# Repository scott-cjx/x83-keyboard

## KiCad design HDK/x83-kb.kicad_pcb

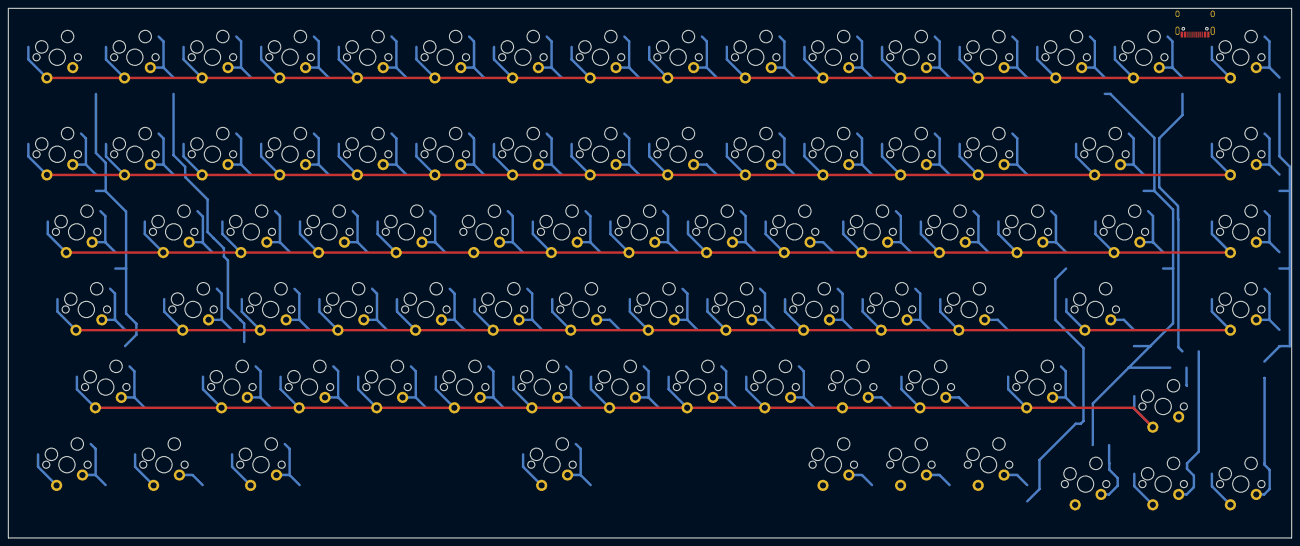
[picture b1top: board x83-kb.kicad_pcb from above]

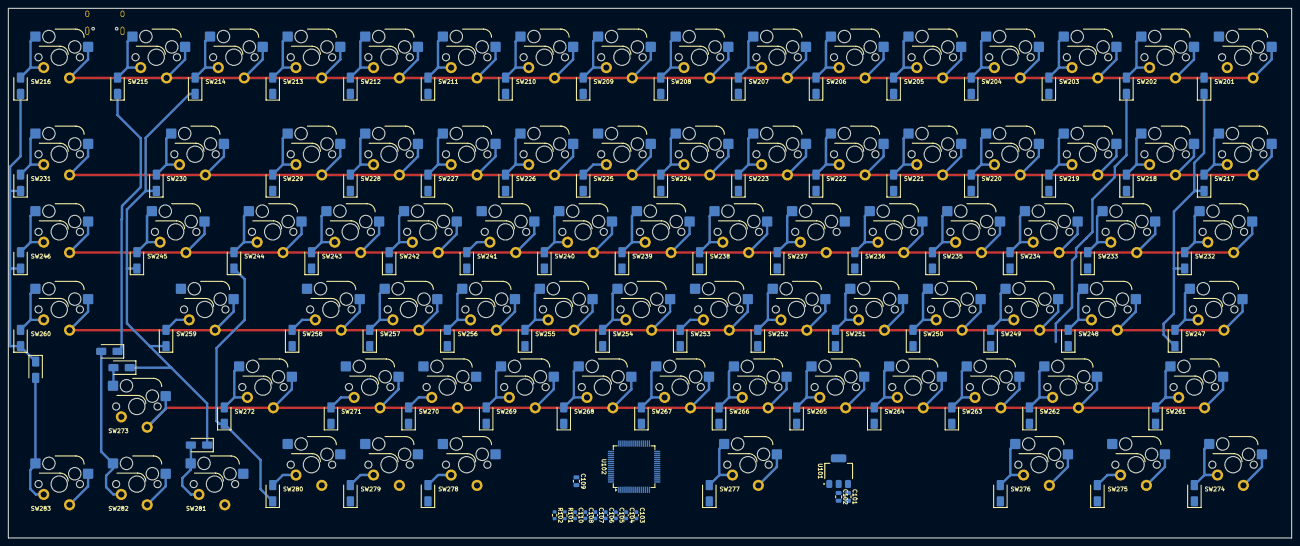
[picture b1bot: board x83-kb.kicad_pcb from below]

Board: 2 copper layers, 315.0 x 130.0 mm, 180 parts (97 on the bottom side), 110 nets.

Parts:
C101, C102, C109: 2u2; C_0805_2012Metric
C103, C104, C105, C106, C107, C108, C110: 100n; C_0603_1608Metric
D201, D202, D203, D204, D205, D206, D207, D208, D209, D210, D211, D212, D213, D214, D215, D216, D217, D218, D219, D220, D221, D222, D223, D224, D225, D226, D227, D228, D229, D230, D231, D232, D233, D234, D235, D236, D237, D238, D239, D240, D241, D242, D243, D244, D245, D246, D247, D248, D249, D250, D251, D252, D253, D254, D255, D256, D257, D258, D259, D260, D261, D262, D263, D264, D265, D266, D267, D268, D269, D270, D271, D272, D273, D274, D275, D276, D277, D278, D279, D280, D281, D282, D283: D; D_SMA
R101, R102: 10K; R_0603_1608Metric
SW201, SW202, SW203, SW204, SW205, SW206, SW207, SW208, SW209, SW210, SW211, SW212, SW213, SW214, SW215, SW216, SW217, SW218, SW219, SW220, SW221, SW222, SW223, SW224, SW225, SW226, SW227, SW228, SW229, SW230, SW231, SW232, SW233, SW234, SW235, SW236, SW237, SW238, SW239, SW240, SW241, SW242, SW243, SW244, SW245, SW246, SW247, SW248, SW249, SW250, SW251, SW252, SW253, SW254, SW255, SW256, SW257, SW258, SW259, SW260, SW261, SW262, SW263, SW264, SW265, SW266, SW267, SW268, SW269, SW270, SW271, SW272, SW273, SW274, SW275, SW276, SW277, SW278, SW279, SW280, SW281, SW282, SW283: SW_OPT_MX
U101: AMS1117-3.3; SOT-223-3_TabPin2
U102: STM32F072RBTx; LQFP-64_10x10mm_P0.5mm

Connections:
+3V3: C102.1, C103.1, C104.1, C105.1, C106.1, C107.1, C108.1, C109.1, R101.1, U101.2 (VO), U102.1 (VBAT), U102.13 (VDDA), U102.19 (VDD), U102.32 (VDD), U102.48 (VDDIO2), U102.64 (VDD)
/BOOT0: R102.1, U102.60 (BOOT0)
/C0: D201.1 (K), D217.1 (K), D232.1 (K), D247.1 (K), D261.1 (K), D274.1 (K), U102.26 (PB0)
/C1: D202.1 (K), D218.1 (K), D233.1 (K), D248.1 (K), D262.1 (K), D275.1 (K), U102.27 (PB1)
/C2: D203.1 (K), D219.1 (K), D234.1 (K), D249.1 (K), D263.1 (K), D276.1 (K), U102.28 (PB2)
/C3: D204.1 (K), D220.1 (K), D235.1 (K), D250.1 (K), D264.1 (K), U102.55 (PB3)
/C4: D205.1 (K), D221.1 (K), D236.1 (K), D251.1 (K), D265.1 (K), U102.56 (PB4)
/C5: D206.1 (K), D222.1 (K), D237.1 (K), D252.1 (K), D266.1 (K), U102.57 (PB5)
/C6: D207.1 (K), D223.1 (K), D238.1 (K), D253.1 (K), D267.1 (K), D277.1 (K), U102.58 (PB6)
/C7: D208.1 (K), D224.1 (K), D239.1 (K), D254.1 (K), D268.1 (K), U102.59 (PB7)
/C8: D209.1 (K), D225.1 (K), D240.1 (K), D255.1 (K), D269.1 (K), U102.61 (PB8)
/C9: D210.1 (K), D226.1 (K), D241.1 (K), D256.1 (K), D270.1 (K), U102.62 (PB9)
/C10: D211.1 (K), D227.1 (K), D242.1 (K), D257.1 (K), D271.1 (K), D278.1 (K), U102.29 (PB10)
/C11: D212.1 (K), D228.1 (K), D243.1 (K), D258.1 (K), D279.1 (K), U102.30 (PB11)
/C12: D213.1 (K), D229.1 (K), D244.1 (K), D272.1 (K), D280.1 (K), U102.33 (PB12)
/C13: D214.1 (K), D230.1 (K), D245.1 (K), D259.1 (K), D273.1 (K), D281.1 (K), U102.34 (PB13)
/C14: D215.1 (K), D282.1 (K), U102.35 (PB14)
/C15: D216.1 (K), D231.1 (K), D246.1 (K), D260.1 (K), D283.1 (K), U102.36 (PB15)
/R0: SW201.1 (B), SW202.1 (B), SW203.1 (B), SW204.1 (B), SW205.1 (B), SW206.1 (B), SW207.1 (B), SW208.1 (B), SW209.1 (B), SW210.1 (B), SW211.1 (B), SW212.1 (B), SW213.1 (B), SW214.1 (B), SW215.1 (B), SW216.1 (B), U102.14 (PA0)
/R1: SW217.1 (B), SW218.1 (B), SW219.1 (B), SW220.1 (B), SW221.1 (B), SW222.1 (B), SW223.1 (B), SW224.1 (B), SW225.1 (B), SW226.1 (B), SW227.1 (B), SW228.1 (B), SW229.1 (B), SW230.1 (B), SW231.1 (B), U102.15 (PA1)
/R2: SW232.1 (B), SW233.1 (B), SW234.1 (B), SW235.1 (B), SW236.1 (B), SW237.1 (B), SW238.1 (B), SW239.1 (B), SW240.1 (B), SW241.1 (B), SW242.1 (B), SW243.1 (B), SW244.1 (B), SW245.1 (B), SW246.1 (B), U102.16 (PA2)
/R3: SW247.1 (B), SW248.1 (B), SW249.1 (B), SW250.1 (B), SW251.1 (B), SW252.1 (B), SW253.1 (B), SW254.1 (B), SW255.1 (B), SW256.1 (B), SW257.1 (B), SW258.1 (B), SW259.1 (B), SW260.1 (B), U102.17 (PA3)
/R4: SW261.1 (B), SW262.1 (B), SW263.1 (B), SW264.1 (B), SW265.1 (B), SW266.1 (B), SW267.1 (B), SW268.1 (B), SW269.1 (B), SW270.1 (B), SW271.1 (B), SW272.1 (B), SW273.1 (B), U102.20 (PA4)
/R5: SW274.1 (B), SW275.1 (B), SW276.1 (B), SW277.1 (B), SW278.1 (B), SW279.1 (B), SW280.1 (B), SW281.1 (B), SW282.1 (B), SW283.1 (B), U102.50 (PA15)
/~NRST: C110.1, R101.2, U102.7 (NRST)
GND: C101.2, C102.2, C103.2, C104.2, C105.2, C106.2, C107.2, C108.2, C109.2, C110.2, R102.2, U101.1 (GND), U102.12 (VSSA), U102.18 (VSS), U102.31 (VSS), U102.47 (VSS), U102.63 (VSS)
unnamed: D201.2 (A), SW201.2 (A)
unnamed: D202.2 (A), SW202.2 (A)
unnamed: D203.2 (A), SW203.2 (A)
unnamed: D204.2 (A), SW204.2 (A)
unnamed: D205.2 (A), SW205.2 (A)
unnamed: D206.2 (A), SW206.2 (A)
unnamed: D207.2 (A), SW207.2 (A)
unnamed: D208.2 (A), SW208.2 (A)
unnamed: D209.2 (A), SW209.2 (A)
unnamed: D210.2 (A), SW210.2 (A)
unnamed: D211.2 (A), SW211.2 (A)
unnamed: D212.2 (A), SW212.2 (A)
unnamed: D213.2 (A), SW213.2 (A)
unnamed: D214.2 (A), SW214.2 (A)
unnamed: D215.2 (A), SW215.2 (A)
unnamed: D216.2 (A), SW216.2 (A)
unnamed: D217.2 (A), SW217.2 (A)
unnamed: D218.2 (A), SW218.2 (A)
unnamed: D219.2 (A), SW219.2 (A)
unnamed: D220.2 (A), SW220.2 (A)
unnamed: D221.2 (A), SW221.2 (A)
unnamed: D222.2 (A), SW222.2 (A)
unnamed: D223.2 (A), SW223.2 (A)
unnamed: D224.2 (A), SW224.2 (A)
unnamed: D225.2 (A), SW225.2 (A)
unnamed: D226.2 (A), SW226.2 (A)
unnamed: D227.2 (A), SW227.2 (A)
unnamed: D228.2 (A), SW228.2 (A)
unnamed: D229.2 (A), SW229.2 (A)
unnamed: D230.2 (A), SW230.2 (A)
unnamed: D231.2 (A), SW231.2 (A)
unnamed: D232.2 (A), SW232.2 (A)
unnamed: D233.2 (A), SW233.2 (A)
unnamed: D234.2 (A), SW234.2 (A)
unnamed: D235.2 (A), SW235.2 (A)
unnamed: D236.2 (A), SW236.2 (A)
unnamed: D237.2 (A), SW237.2 (A)
unnamed: D238.2 (A), SW238.2 (A)
unnamed: D239.2 (A), SW239.2 (A)
unnamed: D240.2 (A), SW240.2 (A)
unnamed: D241.2 (A), SW241.2 (A)
unnamed: D242.2 (A), SW242.2 (A)
unnamed: D243.2 (A), SW243.2 (A)
unnamed: D244.2 (A), SW244.2 (A)
unnamed: D245.2 (A), SW245.2 (A)
unnamed: D246.2 (A), SW246.2 (A)
unnamed: D247.2 (A), SW247.2 (A)
unnamed: D248.2 (A), SW248.2 (A)
unnamed: D249.2 (A), SW249.2 (A)
unnamed: D250.2 (A), SW250.2 (A)
unnamed: D251.2 (A), SW251.2 (A)
unnamed: D252.2 (A), SW252.2 (A)
unnamed: D253.2 (A), SW253.2 (A)
unnamed: D254.2 (A), SW254.2 (A)
unnamed: D255.2 (A), SW255.2 (A)
unnamed: D256.2 (A), SW256.2 (A)
unnamed: D257.2 (A), SW257.2 (A)
unnamed: D258.2 (A), SW258.2 (A)
unnamed: D259.2 (A), SW259.2 (A)
unnamed: D260.2 (A), SW260.2 (A)
unnamed: D261.2 (A), SW261.2 (A)
unnamed: D262.2 (A), SW262.2 (A)
unnamed: D263.2 (A), SW263.2 (A)
unnamed: D264.2 (A), SW264.2 (A)
unnamed: D265.2 (A), SW265.2 (A)
unnamed: D266.2 (A), SW266.2 (A)
unnamed: D267.2 (A), SW267.2 (A)
unnamed: D268.2 (A), SW268.2 (A)
unnamed: D269.2 (A), SW269.2 (A)
unnamed: D270.2 (A), SW270.2 (A)
unnamed: D271.2 (A), SW271.2 (A)
unnamed: D272.2 (A), SW272.2 (A)
unnamed: D273.2 (A), SW273.2 (A)
unnamed: D274.2 (A), SW274.2 (A)
unnamed: D275.2 (A), SW275.2 (A)
unnamed: D276.2 (A), SW276.2 (A)
unnamed: D277.2 (A), SW277.2 (A)
unnamed: D278.2 (A), SW278.2 (A)
unnamed: D279.2 (A), SW279.2 (A)
unnamed: D280.2 (A), SW280.2 (A)
unnamed: D281.2 (A), SW281.2 (A)
unnamed: D282.2 (A), SW282.2 (A)
unnamed: D283.2 (A), SW283.2 (A)
VCC: C101.1, U101.3 (VI)

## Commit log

2024-04-26 Initialize gh-pages
2024-04-26 Moving files docs/* LICENSE using main
2024-04-26 Deploying to gh-pages from @ scott-cjx/x83-keyboard@0edaa5d0bbe5e405b1ef01ef9df371c59fcc67e6 🚀
2024-04-26 init commit
2024-04-26 Deploying to gh-pages from @ scott-cjx/x83-keyboard@016eb6315f94249fef3d56b30d6df5a498c30094 🚀
2024-04-29 added rsc
2024-04-29 rm lck files
2024-04-29 Deploying to gh-pages from @ scott-cjx/x83-keyboard@73fd805fa4abb6ba17e2ecaddae99ee9325b6da3 🚀
2024-04-29 updated pcb
2024-04-29 Deploying to gh-pages from @ scott-cjx/x83-keyboard@dda6698f273733aa4d7bcb3a2faf33f4a6f7e3ec 🚀
2024-04-29 Deploying to gh-pages from @ scott-cjx/x83-keyboard@52e6c5fd14339503ad1b087b6b5392dc03c37765 🚀
2024-04-29 added models
2024-04-29 Deploying to gh-pages from @ scott-cjx/x83-keyboard@13d6258d854cf3e37925bcac8deea261b25093c3 🚀
2024-05-02 updated diodes
2024-05-02 Deploying to gh-pages from @ scott-cjx/x83-keyboard@1b588e3b12cc682ba4081c207e8616cc04a01c73 🚀
2024-05-21 modified docs
2024-05-21 Deploying to gh-pages from @ scott-cjx/x83-keyboard@dcd99acfd90e1f0e7a4b6f57b79a7d0f74d9827c 🚀
